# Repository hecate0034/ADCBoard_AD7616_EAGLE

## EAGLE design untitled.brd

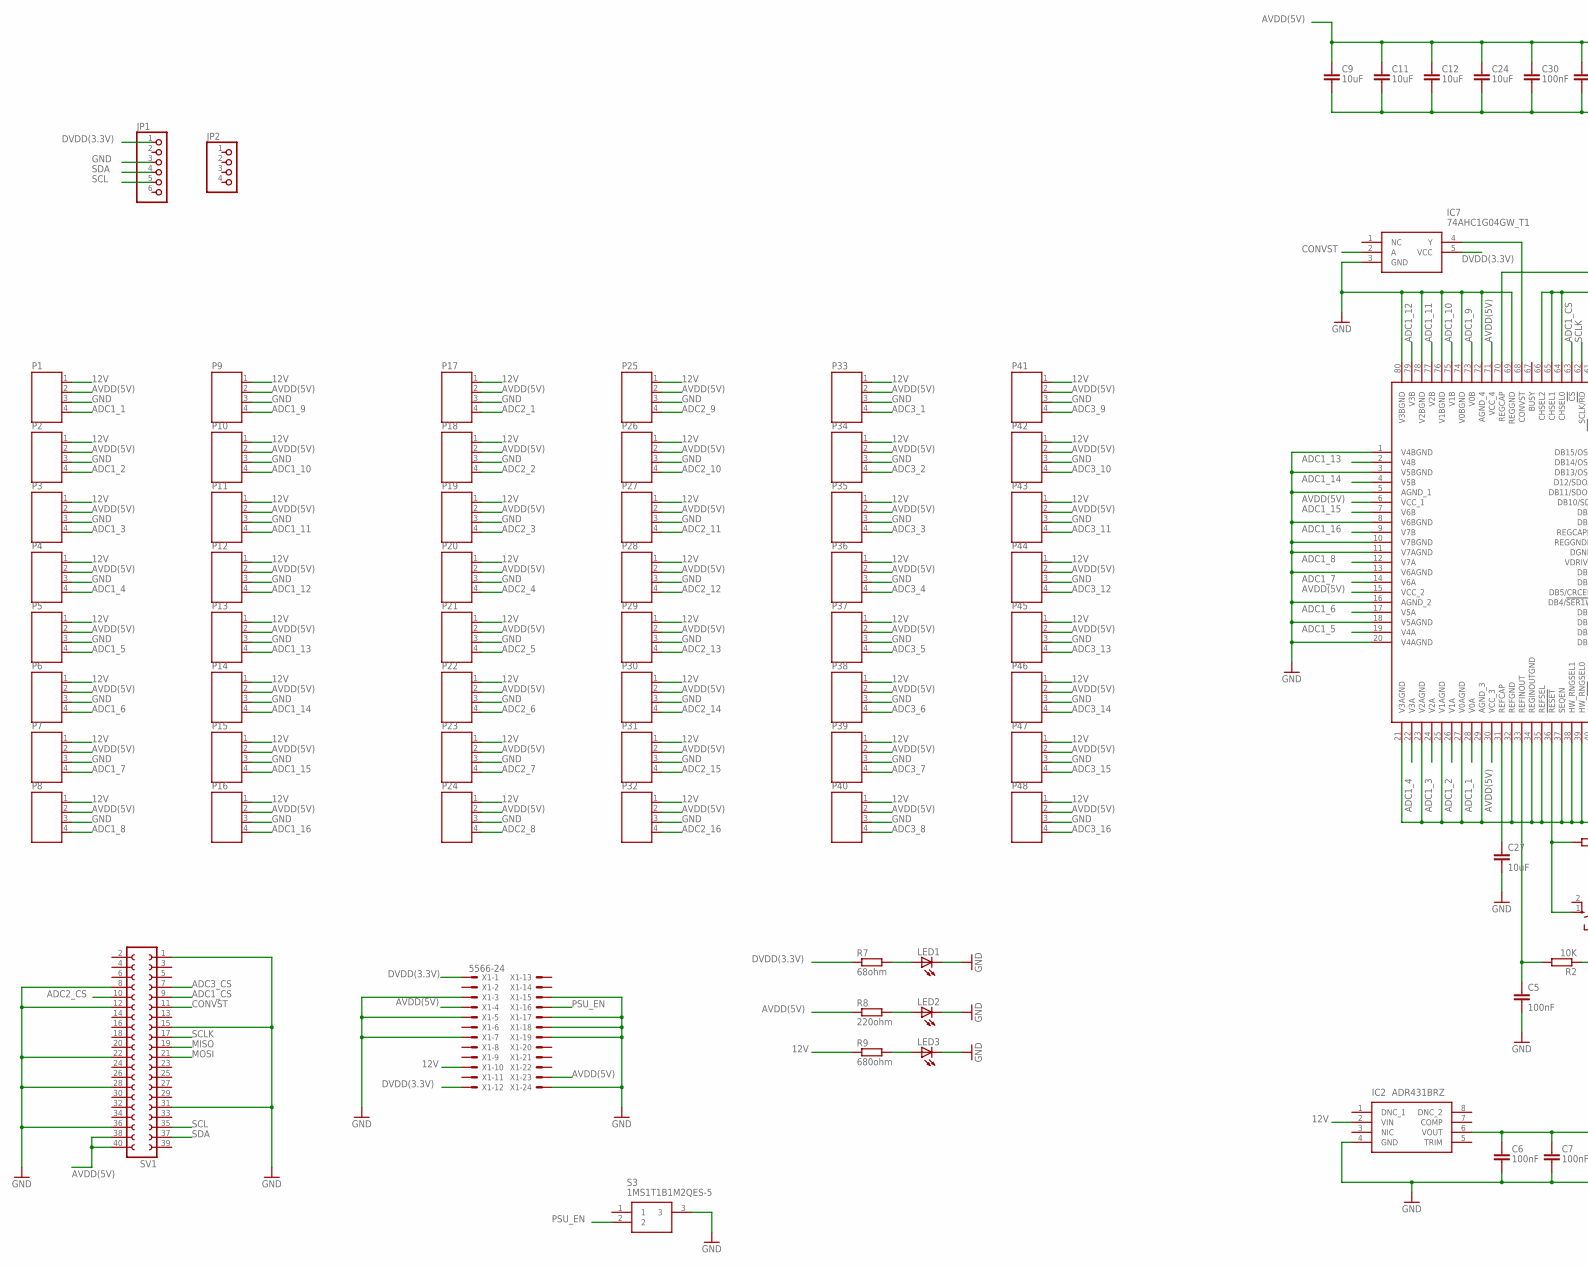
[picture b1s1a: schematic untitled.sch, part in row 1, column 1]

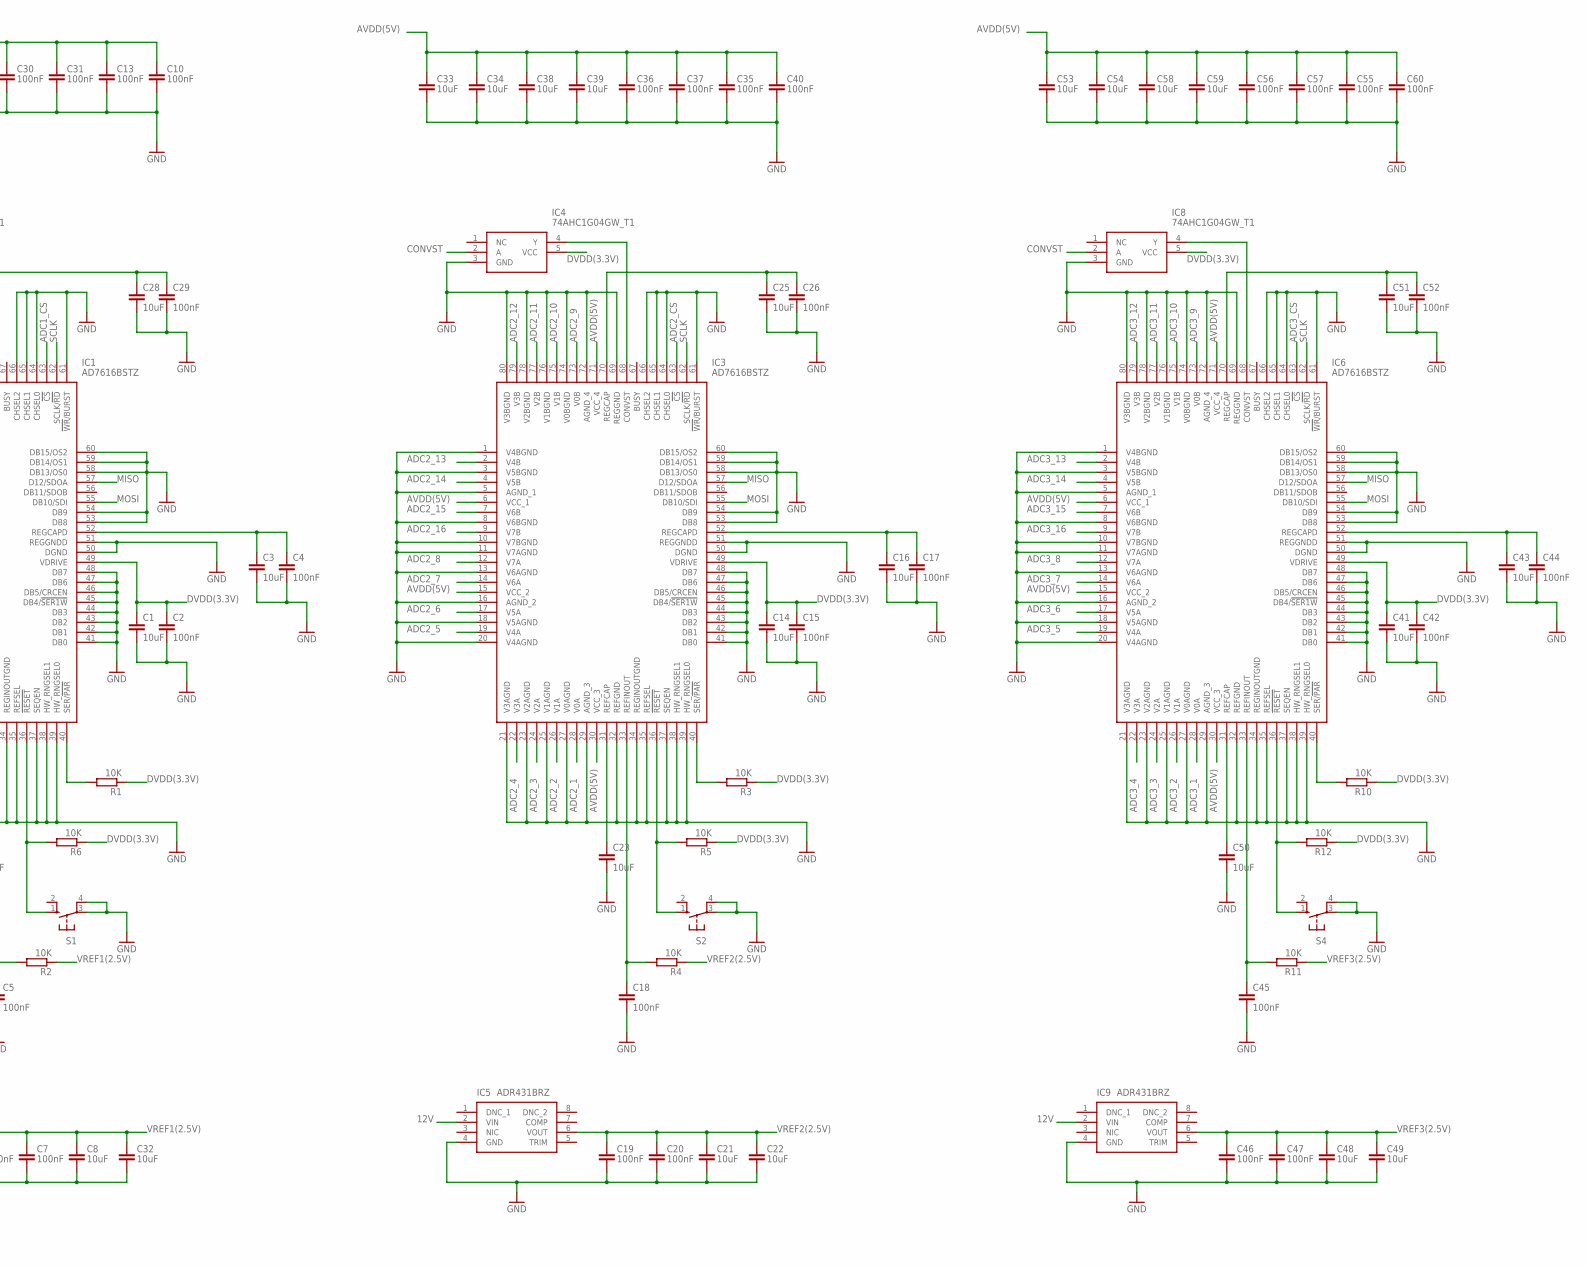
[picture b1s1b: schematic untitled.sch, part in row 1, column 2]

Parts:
C1, C3, C8, C9, C11, C12, C14, C16, C21, C22, C23, C24, C25, C27, C28, C32, C33, C34, C38, C39, C41, C43, C48, C49, C50, C51, C53, C54, C58, C59: 10uF; C1206
C2, C4, C5, C6, C7, C10, C13, C15, C17, C18, C19, C20, C26, C29, C30, C31, C35, C36, C37, C40, C42, C44, C45, C46, C47, C52, C55, C56, C57, C60: 100nF; C0603
IC1, IC3, IC6: AD7616BSTZ; QFP65P1600X1600X160-80N
IC2, IC5, IC9: ADR431BRZ; SOIC127P600X175-8N
IC4, IC7, IC8: 74AHC1G04GW_T1; SOT65P212X110-5N
JP1: PINHD-1X6; 1X06
JP2: PINHD-1X4; 1X04
LED1, LED2, LED3: LEDCHIPLED_0603; CHIPLED_0603
P1, P2, P3, P4, P5, P6, P7, P8, P9, P10, P11, P12, P13, P14, P15, P16, P17, P18, P19, P20, P21, P22, P23, P24, P25, P26, P27, P28, P29, P30, P31, P32, P33, P34, P35, P36, P37, P38, P39, P40, P41, P42, P43, P44, P45, P46, P47, P48: JST-PH4
R1, R2, R3, R4, R5, R6, R10, R11, R12: 10K; R0603
R7: 68ohm; R0805
R8: 220ohm; R0805
R9: 680ohm; R0805
S1, S2, S4: 10-XX; B3F-10XX
S3: 1MS1T1B1M2QES-5
SV1: FE20-2
X1: 5566-24

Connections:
12V: IC2.2 (VIN), IC5.2 (VIN), IC9.2 (VIN), P1.1, P2.1, P3.1, P4.1, P5.1, P6.1, P7.1, P8.1, P9.1, P10.1, P11.1, P12.1, P13.1, P14.1, P15.1, P16.1, P17.1, P18.1, P19.1, P20.1, P21.1, P22.1, P23.1, P24.1, P25.1, P26.1, P27.1, P28.1, P29.1, P30.1, P31.1, P32.1, P33.1, P34.1, P35.1, P36.1, P37.1, P38.1, P39.1, P40.1, P41.1, P42.1, P43.1, P44.1, P45.1, P46.1, P47.1, P48.1, R9.1, X1.10
!RESET1: IC1.36 (!RESET), R6.2, S1.1 (S)
!RESET2: IC3.36 (!RESET), R5.2, S2.1 (S)
!RESET3: IC6.36 (!RESET), R12.2, S4.1 (S)
ADC1_1: IC1.28 (V0A), P1.4
ADC1_2: IC1.26 (V1A), P2.4
ADC1_3: IC1.24 (V2A), P3.4
ADC1_4: IC1.22 (V3A), P4.4
ADC1_5: IC1.19 (V4A), P5.4
ADC1_6: IC1.17 (V5A), P6.4
ADC1_7: IC1.14 (V6A), P7.4
ADC1_8: IC1.12 (V7A), P8.4
ADC1_9: IC1.73 (V0B), P9.4
ADC1_10: IC1.75 (V1B), P10.4
ADC1_11: IC1.77 (V2B), P11.4
ADC1_12: IC1.79 (V3B), P12.4
ADC1_13: IC1.2 (V4B), P13.4
ADC1_14: IC1.4 (V5B), P14.4
ADC1_15: IC1.7 (V6B), P15.4
ADC1_16: IC1.9 (V7B), P16.4
ADC1_CS: IC1.63 (!CS), SV1.9
ADC2_1: IC3.28 (V0A), P17.4
ADC2_2: IC3.26 (V1A), P18.4
ADC2_3: IC3.24 (V2A), P19.4
ADC2_4: IC3.22 (V3A), P20.4
ADC2_5: IC3.19 (V4A), P21.4
ADC2_6: IC3.17 (V5A), P22.4
ADC2_7: IC3.14 (V6A), P23.4
ADC2_8: IC3.12 (V7A), P24.4
ADC2_9: IC3.73 (V0B), P25.4
ADC2_10: IC3.75 (V1B), P26.4
ADC2_11: IC3.77 (V2B), P27.4
ADC2_12: IC3.79 (V3B), P28.4
ADC2_13: IC3.2 (V4B), P29.4
ADC2_14: IC3.4 (V5B), P30.4
ADC2_15: IC3.7 (V6B), P31.4
ADC2_16: IC3.9 (V7B), P32.4
ADC2_CS: IC3.63 (!CS), SV1.10
ADC3_1: IC6.28 (V0A), P33.4
ADC3_2: IC6.26 (V1A), P34.4
ADC3_3: IC6.24 (V2A), P35.4
ADC3_4: IC6.22 (V3A), P36.4
ADC3_5: IC6.19 (V4A), P37.4
ADC3_6: IC6.17 (V5A), P38.4
ADC3_7: IC6.14 (V6A), P39.4
ADC3_8: IC6.12 (V7A), P40.4
ADC3_9: IC6.73 (V0B), P41.4
ADC3_10: IC6.75 (V1B), P42.4
ADC3_11: IC6.77 (V2B), P43.4
ADC3_12: IC6.79 (V3B), P44.4
ADC3_13: IC6.2 (V4B), P45.4
ADC3_14: IC6.4 (V5B), P46.4
ADC3_15: IC6.7 (V6B), P47.4
ADC3_16: IC6.9 (V7B), P48.4
ADC3_CS: IC6.63 (!CS), SV1.7
AVDD(5V): C9.1, C10.1, C11.1, C12.1, C13.1, C24.1, C30.1, C31.1, C33.1, C34.1, C35.1, C36.1, C37.1, C38.1, C39.1, C40.1, C53.1, C54.1, C55.1, C56.1, C57.1, C58.1, C59.1, C60.1, IC1.6 (VCC_1), IC1.15 (VCC_2), IC1.30 (VCC_3), IC1.71 (VCC_4), IC3.6 (VCC_1), IC3.15 (VCC_2), IC3.30 (VCC_3), IC3.71 (VCC_4), IC6.6 (VCC_1), IC6.15 (VCC_2), IC6.30 (VCC_3), IC6.71 (VCC_4), P1.2, P2.2, P3.2, P4.2, P5.2, P6.2, P7.2, P8.2, P9.2, P10.2, P11.2, P12.2, P13.2, P14.2, P15.2, P16.2, P17.2, P18.2, P19.2, P20.2, P21.2, P22.2, P23.2, P24.2, P25.2, P26.2, P27.2, P28.2, P29.2, P30.2, P31.2, P32.2, P33.2, P34.2, P35.2, P36.2, P37.2, P38.2, P39.2, P40.2, P41.2, P42.2, P43.2, P44.2, P45.2, P46.2, P47.2, P48.2, R8.1, SV1.38, SV1.40, X1.4, X1.23
CONVST: IC4.2 (A), IC7.2 (A), IC8.2 (A), SV1.11
CONVST1: IC1.68 (CONVST), IC7.4 (Y)
CONVST2: IC3.68 (CONVST), IC4.4 (Y)
CONVST3: IC6.68 (CONVST), IC8.4 (Y)
DVDD(3.3V): C1.1, C2.1, C14.1, C15.1, C41.1, C42.1, IC1.49 (VDRIVE), IC3.49 (VDRIVE), IC4.5 (VCC), IC6.49 (VDRIVE), IC7.5 (VCC), IC8.5 (VCC), JP1.1, R1.1, R3.1, R5.1, R6.1, R7.1, R10.1, R12.1, X1.1, X1.12
GND: C1.2, C2.2, C3.2, C4.2, C5.2, C6.2, C7.2, C8.2, C9.2, C10.2, C11.2, C12.2, C13.2, C14.2, C15.2, C16.2, C17.2, C18.2, C19.2, C20.2, C21.2, C22.2, C23.2, C24.2, C25.2, C26.2, C27.2, C28.2, C29.2, C30.2, C31.2, C32.2, C33.2, C34.2, C35.2, C36.2, C37.2, C38.2, C39.2, C40.2, C41.2, C42.2, C43.2, C44.2, C45.2, C46.2, C47.2, C48.2, C49.2, C50.2, C51.2, C52.2, C53.2, C54.2, C55.2, C56.2, C57.2, C58.2, C59.2, C60.2, IC1.1 (V4BGND), IC1.3 (V5BGND), IC1.5 (AGND_1), IC1.8 (V6BGND), IC1.10 (V7BGND), IC1.11 (V7AGND), IC1.13 (V6AGND), IC1.16 (AGND_2), IC1.18 (V5AGND), IC1.20 (V4AGND), IC1.21 (V3AGND), IC1.23 (V2AGND), IC1.25 (V1AGND), IC1.27 (V0AGND), IC1.29 (AGND_3), IC1.32 (REFGND), IC1.34 (REGINOUTGND), IC1.35 (REFSEL), IC1.37 (SEQEN), IC1.38 (HW_RNGSEL1), IC1.39 (HW_RNGSEL0), IC1.41 (DB0), IC1.42 (DB1), IC1.43 (DB2), IC1.44 (DB3), IC1.45 (DB4/!SER1W), IC1.46 (DB5/CRCEN), IC1.47 (DB6), IC1.48 (DB7), IC1.50 (DGND), IC1.51 (REGGNDD), IC1.53 (DB8), IC1.54 (DB9), IC1.58 (DB13/OS0), IC1.59 (DB14/OS1), IC1.60 (DB15/OS2), IC1.61 (!WR!/BURST), IC1.64 (CHSEL0), IC1.65 (CHSEL1), IC1.66 (CHSEL2), IC1.69 (REGGND), IC1.72 (AGND_4), IC1.74 (V0BGND), IC1.76 (V1BGND), IC1.78 (V2BGND), IC1.80 (V3BGND), IC2.4 (GND), IC3.1 (V4BGND), IC3.3 (V5BGND), IC3.5 (AGND_1), IC3.8 (V6BGND), IC3.10 (V7BGND), IC3.11 (V7AGND), IC3.13 (V6AGND), IC3.16 (AGND_2), IC3.18 (V5AGND), IC3.20 (V4AGND), IC3.21 (V3AGND), IC3.23 (V2AGND), IC3.25 (V1AGND), IC3.27 (V0AGND), IC3.29 (AGND_3), IC3.32 (REFGND), IC3.34 (REGINOUTGND), IC3.35 (REFSEL), IC3.37 (SEQEN), IC3.38 (HW_RNGSEL1), IC3.39 (HW_RNGSEL0), IC3.41 (DB0), IC3.42 (DB1), IC3.43 (DB2), IC3.44 (DB3), IC3.45 (DB4/!SER1W), IC3.46 (DB5/CRCEN), IC3.47 (DB6), IC3.48 (DB7), IC3.50 (DGND), IC3.51 (REGGNDD), IC3.53 (DB8), IC3.54 (DB9), IC3.58 (DB13/OS0), IC3.59 (DB14/OS1), IC3.60 (DB15/OS2), IC3.61 (!WR!/BURST), IC3.64 (CHSEL0), IC3.65 (CHSEL1), IC3.66 (CHSEL2), IC3.69 (REGGND), IC3.72 (AGND_4), IC3.74 (V0BGND), IC3.76 (V1BGND), IC3.78 (V2BGND), IC3.80 (V3BGND), IC4.3 (GND), IC5.4 (GND), IC6.1 (V4BGND), IC6.3 (V5BGND), IC6.5 (AGND_1), IC6.8 (V6BGND), IC6.10 (V7BGND), IC6.11 (V7AGND), IC6.13 (V6AGND), IC6.16 (AGND_2), IC6.18 (V5AGND), IC6.20 (V4AGND), IC6.21 (V3AGND), IC6.23 (V2AGND), IC6.25 (V1AGND), IC6.27 (V0AGND), IC6.29 (AGND_3), IC6.32 (REFGND), IC6.34 (REGINOUTGND), IC6.35 (REFSEL), IC6.37 (SEQEN), IC6.38 (HW_RNGSEL1), IC6.39 (HW_RNGSEL0), IC6.41 (DB0), IC6.42 (DB1), IC6.43 (DB2), IC6.44 (DB3), IC6.45 (DB4/!SER1W), IC6.46 (DB5/CRCEN), IC6.47 (DB6), IC6.48 (DB7), IC6.50 (DGND), IC6.51 (REGGNDD), IC6.53 (DB8), IC6.54 (DB9), IC6.58 (DB13/OS0), IC6.59 (DB14/OS1), IC6.60 (DB15/OS2), IC6.61 (!WR!/BURST), IC6.64 (CHSEL0), IC6.65 (CHSEL1), IC6.66 (CHSEL2), IC6.69 (REGGND), IC6.72 (AGND_4), IC6.74 (V0BGND), IC6.76 (V1BGND), IC6.78 (V2BGND), IC6.80 (V3BGND), IC7.3 (GND), IC8.3 (GND), IC9.4 (GND), JP1.3, LED1.C, LED2.C, LED3.C, P1.3, P2.3, P3.3, P4.3, P5.3, P6.3, P7.3, P8.3, P9.3, P10.3, P11.3, P12.3, P13.3, P14.3, P15.3, P16.3, P17.3, P18.3, P19.3, P20.3, P21.3, P22.3, P23.3, P24.3, P25.3, P26.3, P27.3, P28.3, P29.3, P30.3, P31.3, P32.3, P33.3, P34.3, P35.3, P36.3, P37.3, P38.3, P39.3, P40.3, P41.3, P42.3, P43.3, P44.3, P45.3, P46.3, P47.3, P48.3, S1.3, S1.4 (P1), S2.3, S2.4 (P1), S3.3, S4.3, S4.4 (P1), SV1.1, SV1.8, SV1.12, SV1.15, SV1.22, SV1.28, SV1.31, SV1.36, X1.3, X1.5, X1.7, X1.15, X1.17, X1.18, X1.19, X1.24
MISO: IC1.57 (D12/SDOA), IC3.57 (D12/SDOA), IC6.57 (D12/SDOA), SV1.19
MOSI: IC1.55 (DB10/SDI), IC3.55 (DB10/SDI), IC6.55 (DB10/SDI), SV1.21
unnamed: LED2.A, R8.2
unnamed: LED1.A, R7.2
unnamed: LED3.A, R9.2
PSU_EN: S3.2, X1.16
REFCAP1: C27.1, IC1.31 (REFCAP)
REFCAP2: C23.1, IC3.31 (REFCAP)
REFCAP3: C50.1, IC6.31 (REFCAP)
REFINOUT1: C5.1, IC1.33 (REFINOUT), R2.2
REFINOUT2: C18.1, IC3.33 (REFINOUT), R4.2
REFINOUT3: C45.1, IC6.33 (REFINOUT), R11.2
REGCAP1: C28.1, C29.1, IC1.70 (REGCAP)
REGCAP2: C25.1, C26.1, IC3.70 (REGCAP)
REGCAP3: C51.1, C52.1, IC6.70 (REGCAP)
REGCAPD1: C3.1, C4.1, IC1.52 (REGCAPD)
REGCAPD2: C16.1, C17.1, IC3.52 (REGCAPD)
REGCAPD3: C43.1, C44.1, IC6.52 (REGCAPD)
SCL: JP1.5, SV1.35
SCLK: IC1.62 (SCLK/!RD), IC3.62 (SCLK/!RD), IC6.62 (SCLK/!RD), SV1.17
SDA: JP1.4, SV1.37
SER/!PAR1: IC1.40 (SER/!PAR), R1.2
SER/!PAR2: IC3.40 (SER/!PAR), R3.2
SER/!PAR3: IC6.40 (SER/!PAR), R10.2
VREF1(2.5V): C6.1, C7.1, C8.1, C32.1, IC2.6 (VOUT), R2.1
VREF2(2.5V): C19.1, C20.1, C21.1, C22.1, IC5.6 (VOUT), R4.1
VREF3(2.5V): C46.1, C47.1, C48.1, C49.1, IC9.6 (VOUT), R11.1

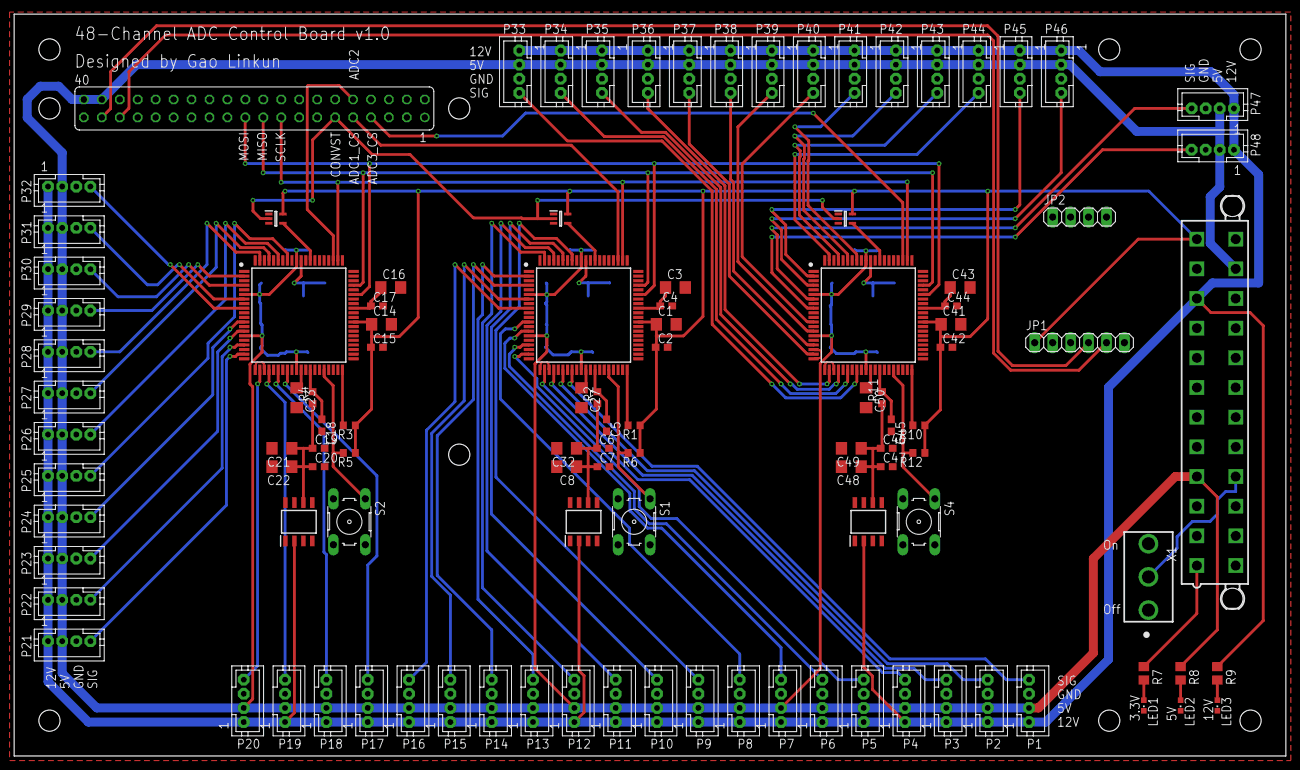
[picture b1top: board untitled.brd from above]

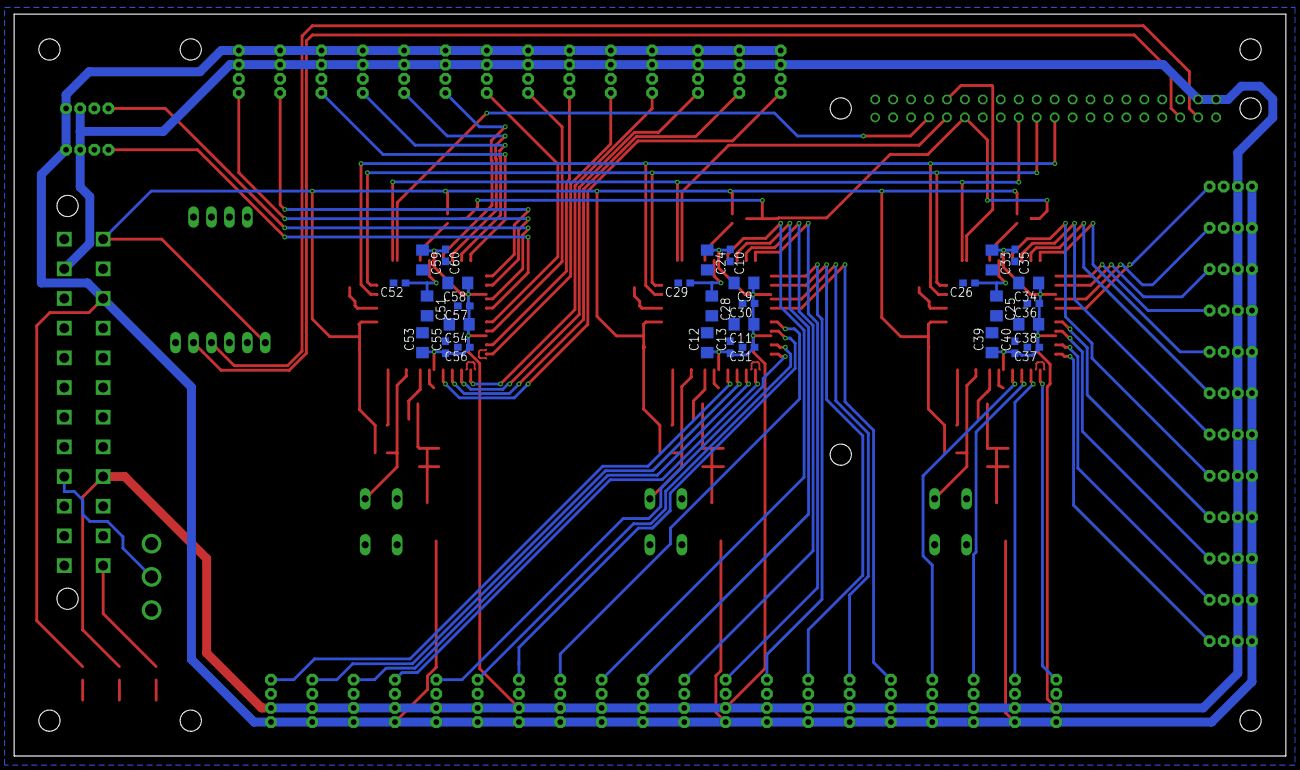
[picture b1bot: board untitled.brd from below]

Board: 4 copper layers, 180.0 x 105.0 mm, 140 parts (30 on the bottom side), 89 nets.
